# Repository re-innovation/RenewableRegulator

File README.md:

# Renewable Regulator

# Overview

This is an open-source project to design a simple, low-cost, Charge Regulator Designs for off-grid renewable energy projects.

A charge-controller protects a re-chargeable battery from over (and sometime under) charging from a renewable energy resource.

This controller will work as a Series and Shunt controller. Future improvements include working as a Maximum Power Point Tracking.
The design is based upon the Arduino IDE and will use one version of the Arduino processors (Arduino Nano initially).
Voltage is measured using a potential divider.
Current is measured using a hall-effect current sensor.
Temperature is measured using a 1-wire digital temperature probe.

A small OLED or LCD screen is used to show the data.
A rotary encoder is used for input data.
Data will also be sent via a serial connection for data-logging use.

## Specifications:

Maximum working voltage: 60V DC
Maximum working current: 50A DC
Measurement accuracy voltage:
Measurement accuracy current:
Temperature: -20 to 150C 0.1C steps

## Contributors

Overview and project concept by Matthew Little (matt@re-innovation.co.uk)
Phase 1 by Arnaud Moulas (arnaud.moulas@gmail.com)
Phase 2 by Yoan Gornes (yoan.gornes@gmail.com)

This project has been part of a larger project for modular power electronics concept initiated by Wind Empowerment:
http://www.wisions.net/projects/exchange-modular-power-to-the-people-democratising-energy-access-through-mo#project121

This section of the project is designed to stand-alone as a charge controller, but the code will be incorporated into the larger project.

# Series Regulator

A series charge controller or series regulator disables further current flow into batteries when they are full.

# Shunt Regulator

A shunt charge controller or shunt regulator diverts excess electricity to an auxiliary or "shunt" load, such as an electric water heater, when batteries are full.

# MPPT Algorithm

At present this function is not included. In the future a DC-DC converter can be used to separately

# Battery types

A rechargeable battery, storage battery, secondary cell, or accumulator is a type of electrical battery which can be charged, discharged into a load, and recharged many times, while a non-rechargeable or primary battery is supplied fully charged, and discarded once discharged. It is composed of one or more electrochemical cells. The term "accumulator" is used as it accumulates and stores energy through a reversible electrochemical reaction. Rechargeable batteries are produced in many different shapes and sizes, ranging from button cells to megawatt systems connected to stabilize an electrical distribution network.
Several different combinations of electrode materials and electrolytes are used, including lead–acid, nickel cadmium (NiCd), nickel metal hydride (NiMH), lithium ion (Li-ion), and lithium ion polymer (Li-ion polymer).

# Data Protocol

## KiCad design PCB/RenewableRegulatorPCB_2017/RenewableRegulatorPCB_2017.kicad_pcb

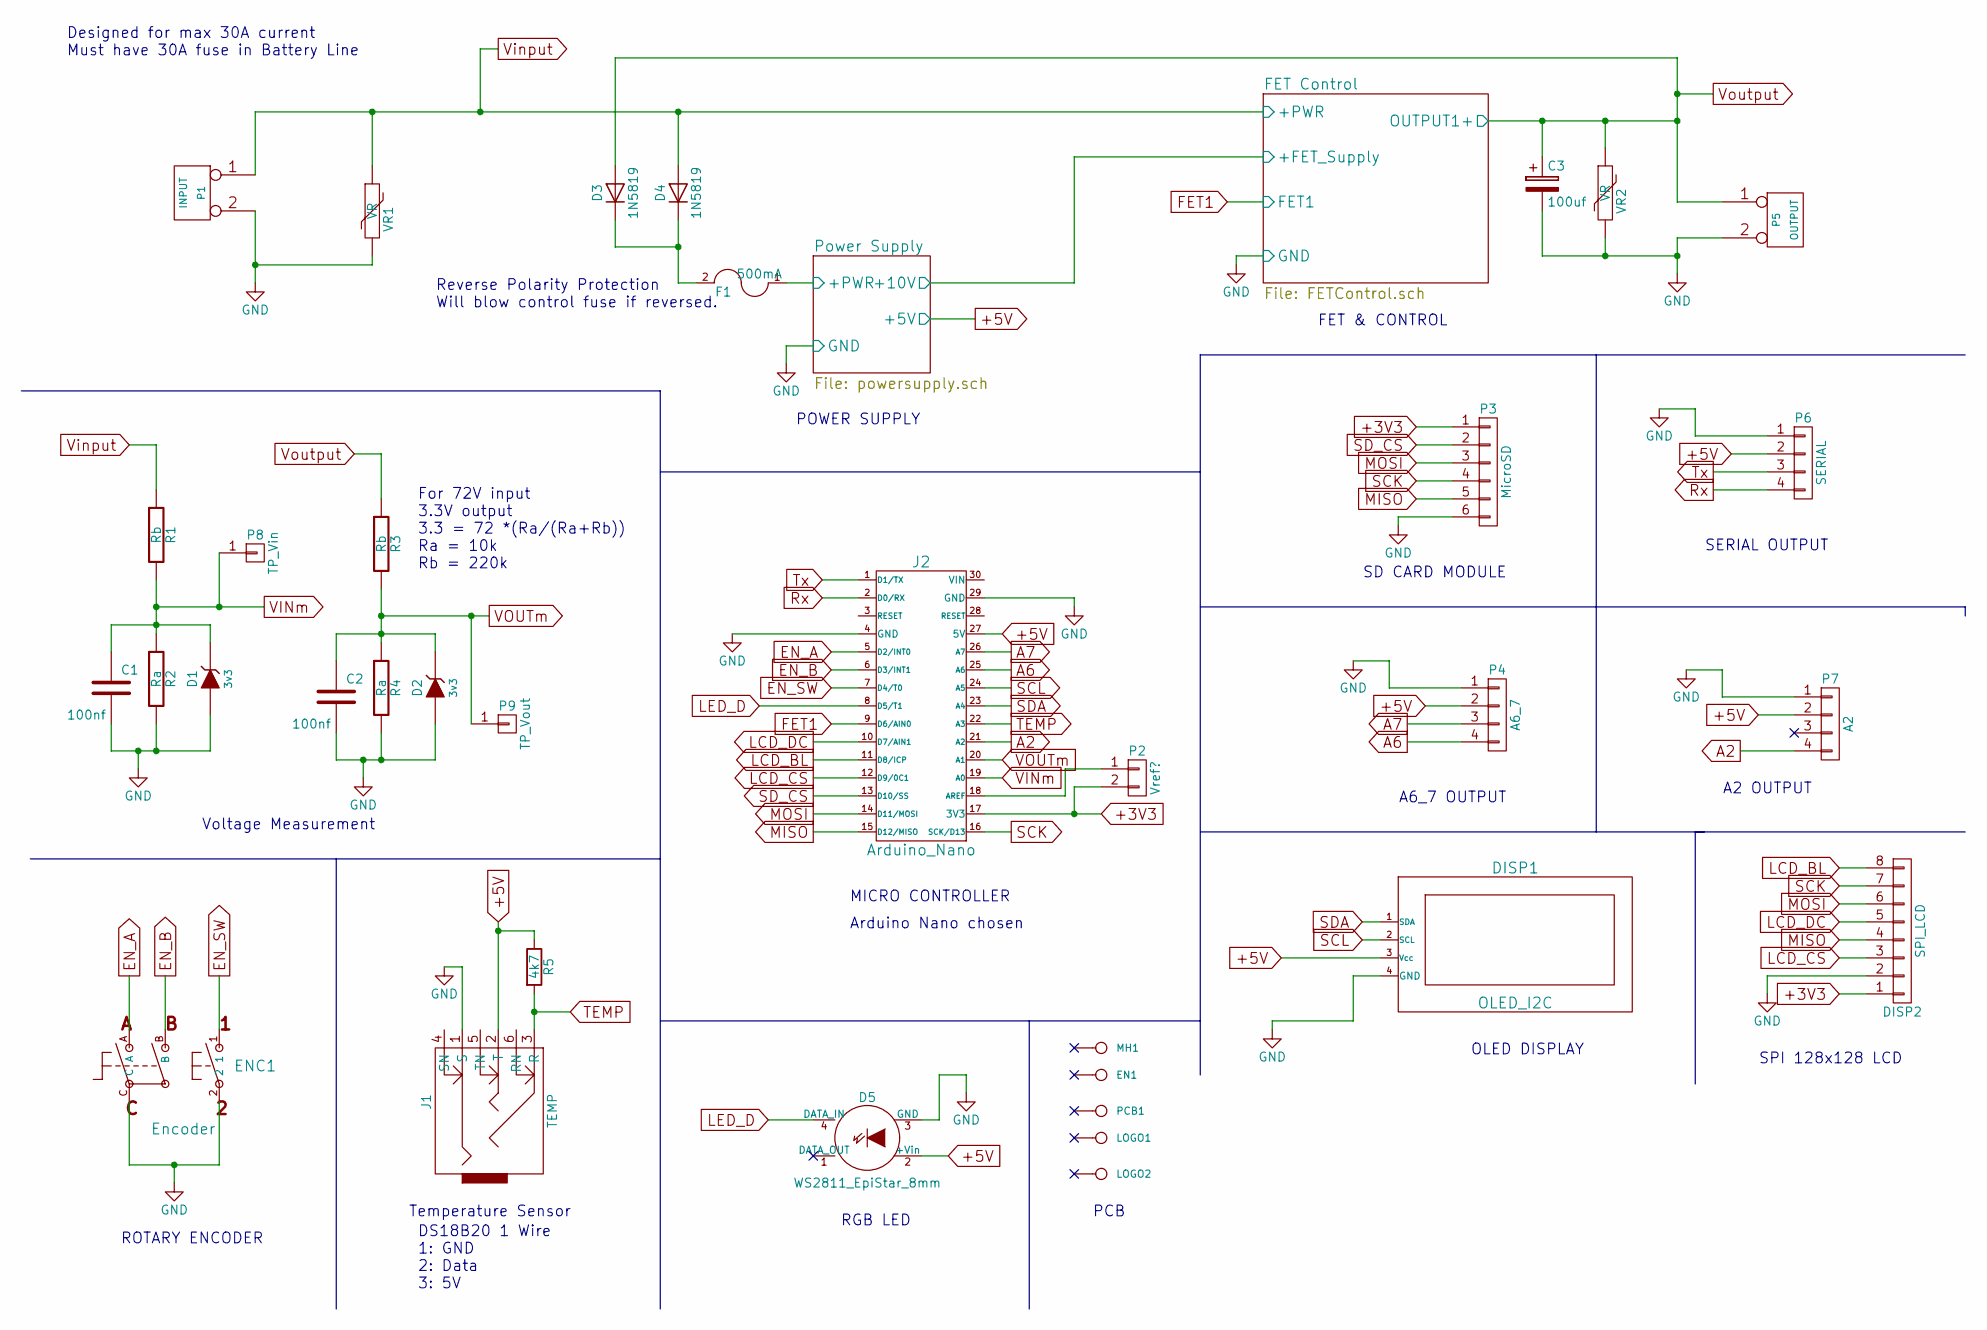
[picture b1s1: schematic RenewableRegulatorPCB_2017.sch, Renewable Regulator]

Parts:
C1, C2: 100nf; C1_wide_lg_pad
C3: 100uf; Capacitor_C_1V7_TH; Manufacturer Part No ECA-2AM101B
D1, D2: 3v3; TH_Diode_1
D3, D4: 1N5819; TH_Diode_1; Manufacturer Part No 1N5819
D5: WS2811_EpiStar_8mm; TH_WS2811_LED_8mm
DISP1: OLED_I2C; TH_OLED1306
DISP2: SPI_LCD; TH_LCD_SPI_128x128
EN1: PCB
ENC1: Encoder; TH_Encoder
F1: 500mA; TH_MC36188_FUSE; Manufacturer Part No RXEF050
J1: TEMP; TH_3_5mm_Jack
J2: Arduino_Nano; NANO_DIP_30_600
LOGO1: LOGO; CEC_Globe_10mm_FCU
LOGO2: LOGO; TCEC_Words_13mm
MH1: Mounting holes
P1: INPUT; Connecteurs_IO_SIL-2_screw_terminal_32A
P2: Vref?; SIL-2_solder_connect
P3: MicroSD; SIL-6_large_pads_marker
P4: A6_7; SIL-4_Grove_SIL
P5: OUTPUT; Connecteurs_IO_SIL-2_screw_terminal_32A
P6: SERIAL; SIL-4_Grove_SIL
P7: A2; SIL-4_Grove_SIL
P8: TP_Vin; 1pin_0_8mm
P9: TP_Vout; 1pin_0_8mm
PCB1: PCB; PCB_75x100mm
R1, R3: Rb; TH_Resistor_1
R2, R4: Ra; TH_Resistor_1
R5: 4k7; TH_Resistor_1
VR1, VR2: VR; TH_MC36188_FUSE; Manufacturer Part No B72214S0500K101

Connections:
+3V3: DISP2.1, J2.17 (3V3), P2.2, P3.1
+5V: D5.2 (+Vin), DISP1.3 (Vcc), J1.2 (T), J2.27 (5V), P4.2, P6.2, P7.2, R5.1; also elsewhere on the board
/Power Supply/+PWR: F1.1; also elsewhere on the board
A2: J2.21 (A2), P7.4
A6: J2.25 (A6), P4.4
A7: J2.26 (A7), P4.3
EN_A: ENC1.A, J2.5 (D2/INT0)
EN_B: ENC1.B, J2.6 (D3/INT1)
EN_SW: ENC1.1, J2.7 (D4/T0)
FET1: J2.9 (D6/AIN0); also elsewhere on the board
GND: C1.2, C2.2, C3.2, D1.1 (A), D2.1 (A), D5.3 (GND), DISP1.4 (GND), DISP2.2, ENC1.2, ENC1.C, J1.1 (S), J2.4 (GND), J2.29 (GND), P1.2, P3.6, P4.1, P5.2, P6.1, P7.1, R2.2, R4.2, VR1.2, VR2.2; also elsewhere on the board
LCD_BL: DISP2.8, J2.11 (D8/ICP)
LCD_CS: DISP2.3, J2.12 (D9/0C1)
LCD_DC: DISP2.5, J2.10 (D7/AIN1)
LED_D: D5.4 (DATA_IN), J2.8 (D5/T1)
MISO: DISP2.4, J2.15 (D12/MISO), P3.5
MOSI: DISP2.6, J2.14 (D11/MOSI), P3.3
unnamed: D3.1 (K), D4.1 (K), F1.2
unnamed: J2.18 (AREF), P2.1
Rx: J2.2 (D0/RX), P6.4
SCK: DISP2.7, J2.16 (SCK/D13), P3.4
SCL: DISP1.2 (SCL), J2.24 (A5)
SDA: DISP1.1 (SDA), J2.23 (A4)
SD_CS: J2.13 (D10/SS), P3.2
TEMP: J1.3 (R), J2.22 (A3), R5.2
Tx: J2.1 (D1/TX), P6.3
VINm: C1.1, D1.2 (K), J2.19 (A0), P8.1, R1.2, R2.1
VOUTm: C2.1, D2.2 (K), J2.20 (A1), P9.1, R3.2, R4.1
Vinput: D4.2 (A), P1.1, R1.1, VR1.1; also elsewhere on the board
Voutput: C3.1, D3.2 (A), P5.1, R3.1, VR2.1; also elsewhere on the board

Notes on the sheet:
PCB
Voltage Measurement
RGB LED
ROTARY ENCODER
OLED DISPLAY
SERIAL OUTPUT
SD CARD MODULE
FET & CONTROL
POWER SUPPLY
MICRO CONTROLLER
Designed for max 30A current Must have 30A fuse in Battery Line
Reverse Polarity Protection Will blow control fuse if reversed.
SPI 128x128 LCD
Temperature Sensor
DS18B20 1 Wire 1: GND 2: Data 3: 5V
A2 OUTPUT
A6_7 OUTPUT
For 72V input 3.3V output 3.3 = 72 *(Ra/(Ra+Rb)) Ra = 10k Rb = 220k
Arduino Nano chosen

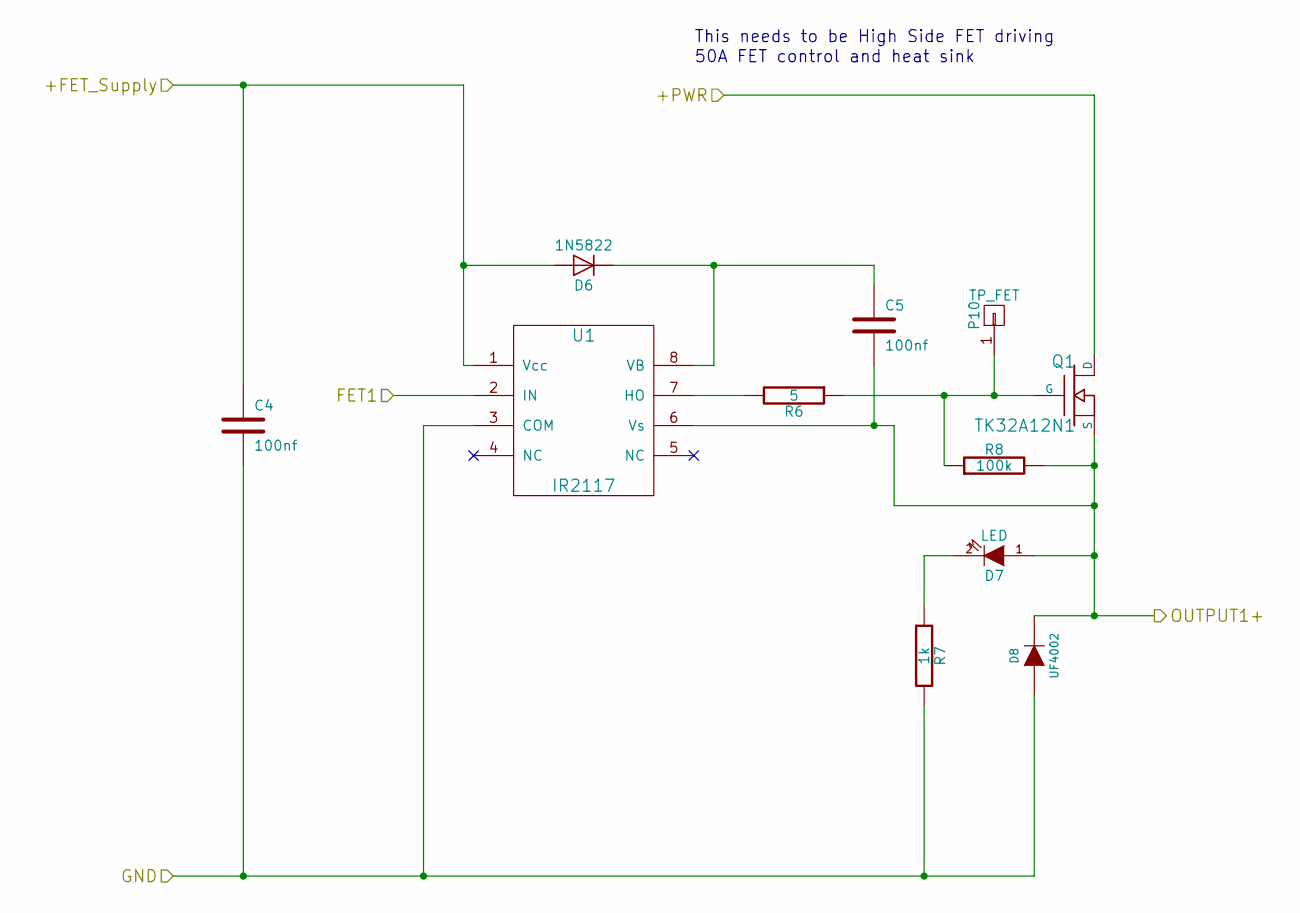
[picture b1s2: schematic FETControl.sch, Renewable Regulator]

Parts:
C4, C5: 100nf; C1_wide_lg_pad
D6: 1N5822; TH_Diode_1; Manufacturer Part No 1N5822
D7: LED; TH_LED-5MM_larg_pad
D8: UF4002; TH_Diode_1; Manufacturer Part No UF4002-E3
P10: TP_FET; 1pin_0_8mm
Q1: TK32A12N1; TO220_VERT_BUZ11_matt; Manufacturer Part No TK32A12N1,S4X
R6: 5; TH_Resistor_1
R7: 1k; TH_Resistor_1
R8: 100k; TH_Resistor_1
U1: IR2117; DIP-8_300_ELL; Manufacturer Part No IR2117PBF

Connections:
/Power Supply/+10V: C4.1, D6.2 (A), U1.1 (Vcc); also elsewhere on the board
FET1: U1.2 (IN); also elsewhere on the board
GND: C4.2, D8.2 (A), R7.2, U1.3 (COM); also elsewhere on the board
unnamed: C5.1, D6.1 (K), U1.8 (VB)
unnamed: D7.2 (K), R7.1
unnamed: P10.1, Q1.G, R6.1, R8.1
unnamed: R6.2, U1.7 (HO)
Vinput: Q1.D; also elsewhere on the board
Voutput: C5.2, D7.1 (A), D8.1 (K), Q1.S, R8.2, U1.6 (Vs); also elsewhere on the board

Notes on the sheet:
This needs to be High Side FET driving
50A FET control and heat sink

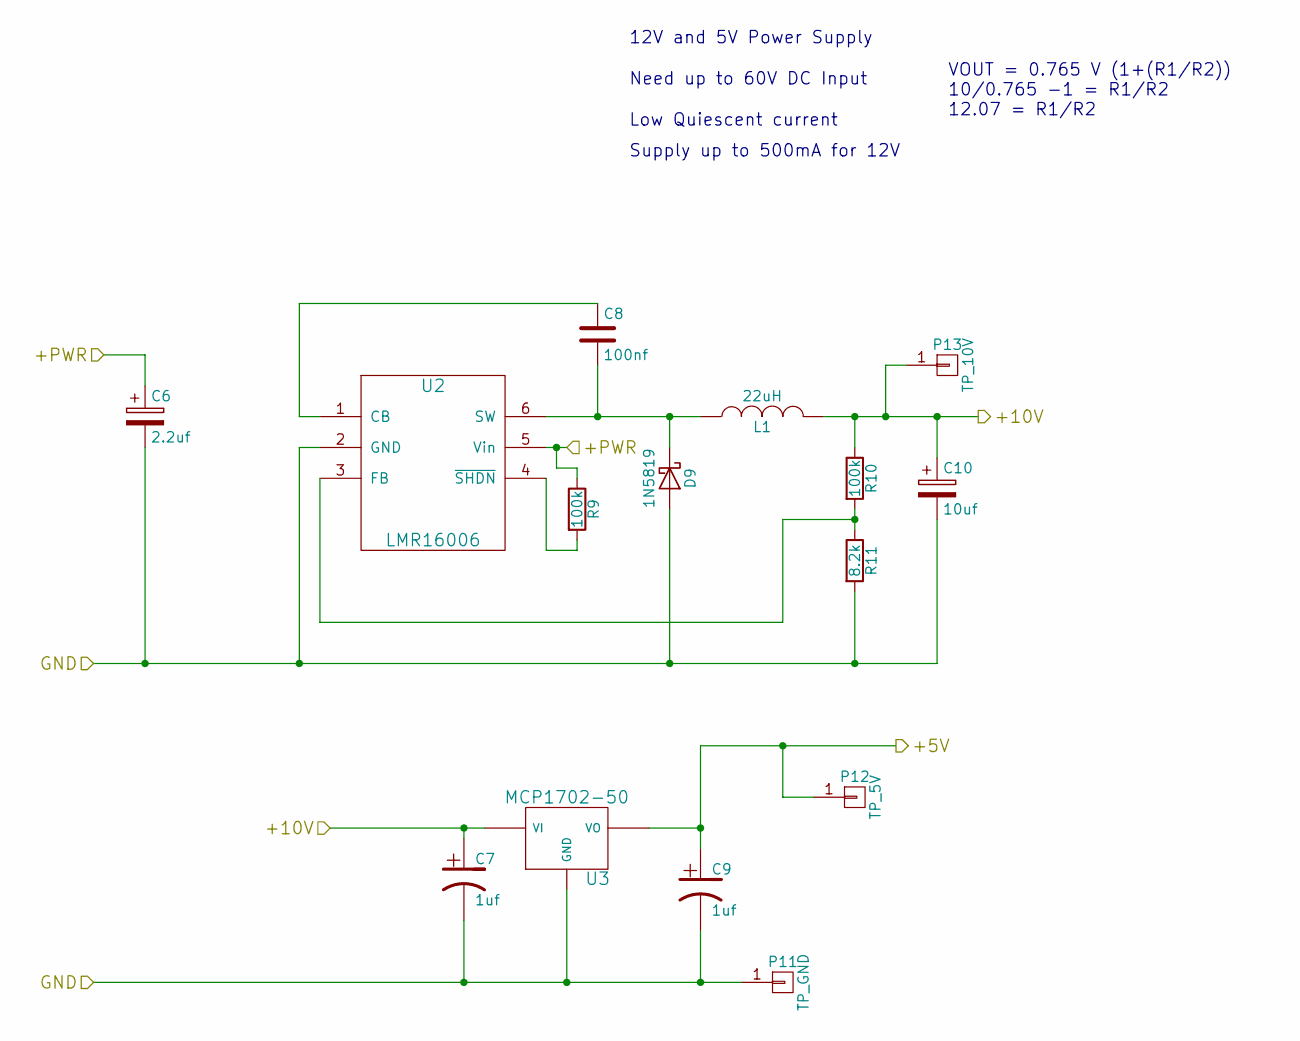
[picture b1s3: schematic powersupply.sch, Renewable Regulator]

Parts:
C6: 2.2uf; Capacitor_C6_1V7_TH; Manufacturer Part No RDEC72A225K3M1H03A
C7: 1uf; Capacitor_C7_1V7_TH; Manufacturer Part No RCER71H105K2M1H03A
C8: 100nf; C1_wide_lg_pad
C9: 1uf; Capacitor_C9_1V7_TH; Manufacturer Part No RCER71H105K2M1H03A
C10: 10uf; Capacitor_C10_1V7_TH; Manufacturer Part No EEUFR1H100
D9: 1N5819; TH_Diode_1; Manufacturer Part No 1N5819
L1: 22uH; TH_Inductor; Manufacturer Part No 744772220
P11: TP_GND; 1pin_0_8mm
P12: TP_5V; 1pin_0_8mm
P13: TP_10V; 1pin_0_8mm
R9, R10: 100k; TH_Resistor_1
R11: 8.2k; TH_Resistor_1
U2: LMR16006; SM_SOT23-6; Manufacturer Part No LMR16006YDDCT
U3: MCP1702-50; TO92_MCP9701_matt; Manufacturer Part No MCP1702-5002E/TO

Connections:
+5V: C9.1, P12.1, U3.VO; also elsewhere on the board
/Power Supply/+10V: C7.1, C10.1, L1.2, P13.1, R10.1, U3.VI; also elsewhere on the board
/Power Supply/+PWR: C6.1, R9.1, U2.5 (Vin); also elsewhere on the board
GND: C6.2, C7.2, C9.2, C10.2, D9.2 (A), P11.1, R11.2, U2.2 (GND), U3.GND; also elsewhere on the board
unnamed: C8.1, U2.1 (CB)
unnamed: C8.2, D9.1 (K), L1.1, U2.6 (SW)
unnamed: R9.2, U2.4 (~SHDN)
unnamed: R10.2, R11.1, U2.3 (FB)

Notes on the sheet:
12V and 5V Power Supply
Need up to 60V DC Input
Low Quiescent current
Supply up to 500mA for 12V
VOUT = 0.765 V (1+(R1/R2)) 10/0.765 -1 = R1/R2 12.07 = R1/R2

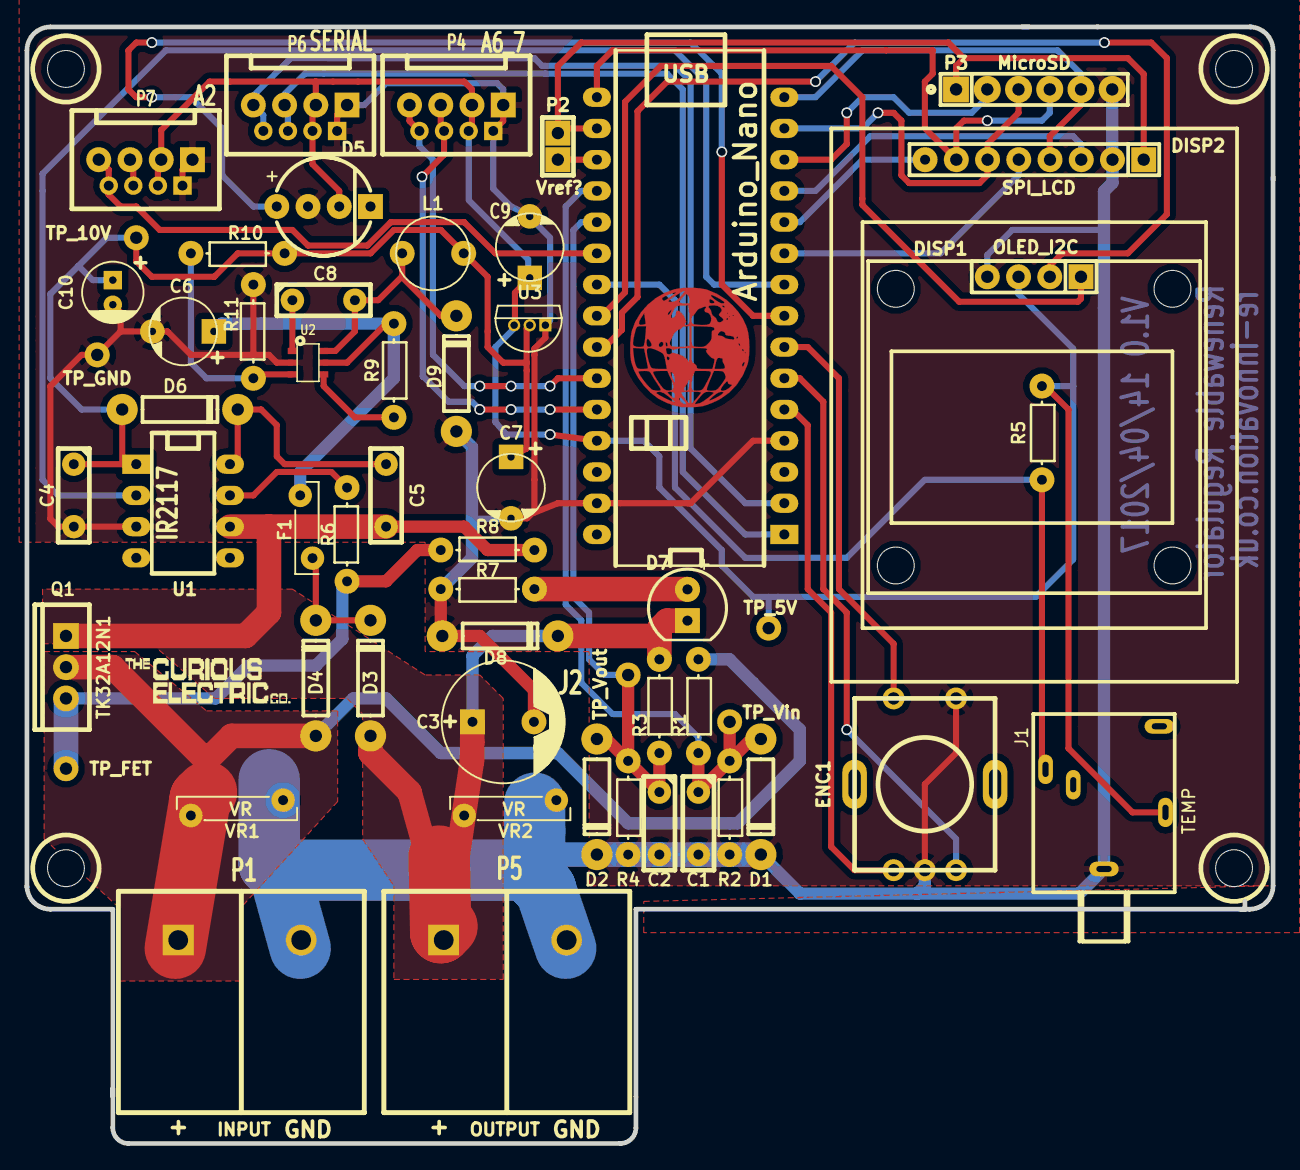
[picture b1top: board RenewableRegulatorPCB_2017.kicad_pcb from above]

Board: 2 copper layers, 101.3 x 90.8 mm, 62 parts (0 on the bottom side), 39 nets.

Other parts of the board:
MH1#2, MH1#3, MH1#4: CONN_1; 3mm_hole

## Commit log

2016-06-15 First Upload from Arnaud
    Algorithm
    Documentation
    Libraries
2017-04-03 Updated files for Yoan
    Added PCB. Removed .word report from Arnaud
2017-04-03 EEPROMEx and LD5110_Graph libraries changed
2017-04-03 Clean Code + Arnaud's comments that was in the code but not used
2017-04-04 Code with rotary encoder
2017-04-04 Updated PCB
    First version of schematic. Needs review
2017-04-05 Moved code into new file structure
2017-04-05 Update of metal box
2017-04-05 Large update of PCB design
2017-04-07 First Version of PCB
2017-04-10 Secod
2017-04-10 Added MH and footprints
2017-04-11 Third Version of PCB
2017-04-12 BOM uploaded
2017-04-12 uploaded libraries
2017-04-13 code with nice curve uploaded
2017-04-14 Updated PCB and schematic
    WS2811 LED swapped around Vcc and GND
    OLED swapped around for front mounting
    Tracks cleaned up
2017-04-20 Minor PCb changes. Fit to 100mm x 100mm
2017-04-20 Code uploaded with no global variables
2017-04-20 BOM updated
2017-04-21 SerieShuntController Library + code using this library
2017-04-26 MPPT PCB schematic
2017-04-26 acs712 library
2017-05-05 First version MPPT PCB
2017-05-05 Regulator PCB changes
2017-05-08 Updated PCB of MPPT
2017-05-08 Flow diagram for the series shunt controller
2017-05-19 Updated MPPT PCB
2017-05-31 Last version of regulator PCB
